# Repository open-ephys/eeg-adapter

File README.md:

eeg-adapter
===========

Adapters for using open-ephys for human EEG

Also see the wiki category at https://open-ephys.atlassian.net/wiki/display/OEW/EEG for more info.

Specifications
-----------

EEG breakout board currently supports two connector types: P50 and 40 PIN

- P50 connector Manufactured by EASYCAP (Germany) 
   - **Compatible Systems:** BrainVision (BrainProducts, GmbH) 
   - **Channels:** 32+ channels
   - **Caps:** actiCAP, BrainCap Fast'nEasy, EasyCap, EasyCap active, Fast'nEasy Cap.
   - **Pitch:** 0.05"
   - **Ground:** Third column from the left, first pad at the bottom.
   - **Reference:** First column on the left, 7 pads up from the bottom.

- 40 PIN connector Manufactured by Compumedics Neuroscan (United States)
   - **Compatible Systems:** MagLink, CURRY Scan 7 (Neuroscan, USA)
   - **Channels:** 40+ Channels.
   - **Caps:** Quik-Cap.
   - **Pitch:** 0.1"
   - **Ground:** Bottom row 16 headers in from the left.
   - **Reference:** Top row 7 headers in from the left.

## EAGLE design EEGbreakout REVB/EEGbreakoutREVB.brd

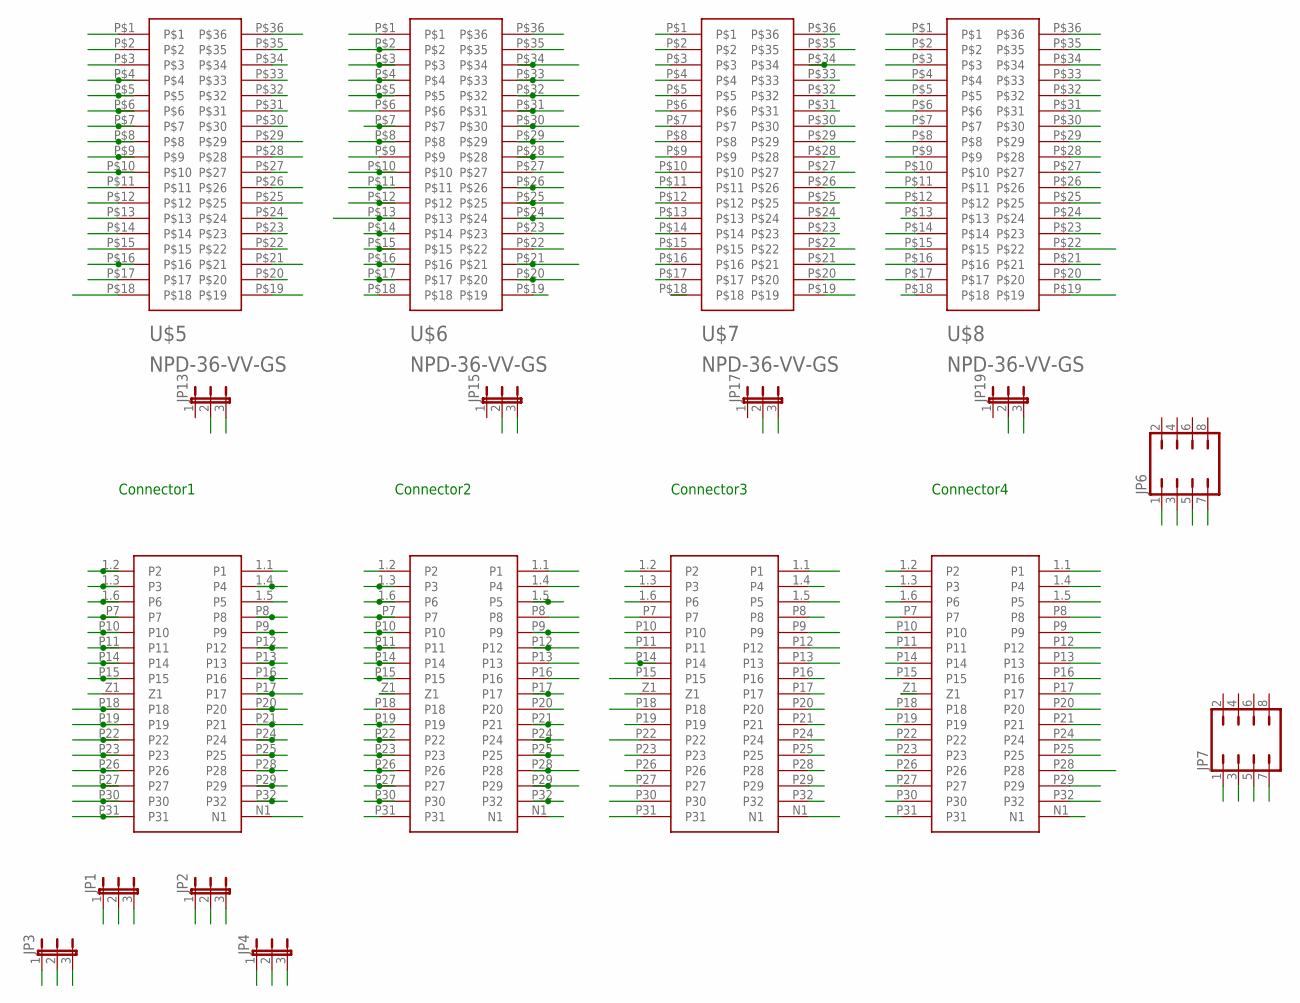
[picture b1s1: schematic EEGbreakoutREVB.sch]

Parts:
JP1, JP2, JP3, JP4, JP13, JP15, JP17, JP19: JP2E; JP2
JP6, JP7: JP4Q
U$1, U$2, U$3, U$4: P50; CON-MOLEX_71061-0003SM
U$5, U$6, U$7, U$8: NPD-36-VV-GS

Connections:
1.1: U$1.1.1 (P1), U$5.P$2
1.2: U$1.1.4 (P4), U$5.P$3
1.3: U$1.1.5 (P5), U$5.P$4
1.4: U$1.P8, U$5.P$5
1.5: U$1.P9, U$5.P$6
1.6: U$1.P12, U$5.P$7
1.7: U$1.P13, U$5.P$8
1.8: U$1.P16, U$5.P$9
1.9: U$1.P17, U$5.P$10
1.10: U$1.P20, U$5.P$11
1.11: U$1.P21, U$5.P$12
1.12: U$1.P24, U$5.P$13
1.13: U$1.P25, U$5.P$14
1.14: U$1.P28, U$5.P$15
1.15: U$1.P29, U$5.P$16
1.16: U$1.P32, U$5.P$17
1.17: U$1.1.2 (P2), U$5.P$20
1.18: U$1.1.3 (P3), U$5.P$21
1.20: U$1.P7, U$5.P$23
1.21: U$1.P10, U$5.P$24
1.22: U$1.P11, U$5.P$25
1.23: U$1.P14, U$5.P$26
1.24: U$1.P15, U$5.P$27
1.25: U$1.P18, U$5.P$28
1.26: U$1.P19, U$5.P$29
1.27: U$1.P22, U$5.P$30
1.28: U$1.P23, U$5.P$31
1.29: JP4.2, U$5.P$32
1.30: JP2.2, U$5.P$33
1.31: JP1.2, U$5.P$34
1.32: JP3.2, U$5.P$35
2.1: U$2.1.1 (P1), U$6.P$2
2.2: U$2.1.4 (P4), U$6.P$3
2.3: U$2.1.5 (P5), U$6.P$4
2.4: U$2.P8, U$6.P$5
2.5: U$2.P9, U$6.P$6
2.6: U$2.P12, U$6.P$7
2.7: U$2.P13, U$6.P$8
2.8: U$2.P16, U$6.P$9
2.9: U$2.P17, U$6.P$10
2.10: U$2.P20, U$6.P$11
2.11: U$2.P21, U$6.P$12
2.12: U$2.P24, U$6.P$13
2.13: U$2.P25, U$6.P$14
2.14: U$2.P28, U$6.P$15
2.15: U$2.P29, U$6.P$16
2.16: U$2.P32, U$6.P$17
2.17: U$2.1.2 (P2), U$6.P$20
2.18: U$2.1.3 (P3), U$6.P$21
2.19: U$2.1.6 (P6), U$6.P$22
2.20: U$2.P7, U$6.P$23
2.21: U$2.P10, U$6.P$24
2.22: U$2.P11, U$6.P$25
2.23: U$2.P14, U$6.P$26
2.24: U$2.P15, U$6.P$27
2.25: U$2.P18, U$6.P$28
2.26: U$2.P19, U$6.P$29
2.27: U$2.P22, U$6.P$30
2.28: U$2.P23, U$6.P$31
2.29: U$2.P26, U$6.P$32
2.30: U$2.P27, U$6.P$33
2.31: U$2.P30, U$6.P$34
2.32: U$2.P31, U$6.P$35
3.1: U$3.1.1 (P1), U$7.P$2
3.2: U$3.1.4 (P4), U$7.P$3
3.3: U$3.1.5 (P5), U$7.P$4
3.4: U$3.P8, U$7.P$5
3.5: U$3.P9, U$7.P$6
3.6: U$3.P12, U$7.P$7
3.7: U$3.P13, U$7.P$8
3.8: U$3.P16, U$7.P$9
3.9: U$3.P17, U$7.P$10
3.10: U$3.P20, U$7.P$11
3.11: U$3.P21, U$7.P$12
3.12: U$3.P24, U$7.P$13
3.13: U$3.P25, U$7.P$14
3.14: U$3.P28, U$7.P$15
3.15: U$3.P29, U$7.P$16
3.16: U$3.P32, U$7.P$17
3.17: U$3.1.2 (P2), U$7.P$20
3.18: U$3.1.3 (P3), U$7.P$21
3.19: U$3.1.6 (P6), U$7.P$22
3.20: U$3.P7, U$7.P$23
3.21: U$3.P10, U$7.P$24
3.22: U$3.P11, U$7.P$25
3.23: U$3.P14, U$7.P$26
3.24: U$3.P15, U$7.P$27
3.25: U$3.P18, U$7.P$28
3.26: U$3.P19, U$7.P$29
3.27: U$3.P22, U$7.P$30
3.28: U$3.P23, U$7.P$31
3.29: U$3.P26, U$7.P$32
3.30: U$3.P27, U$7.P$33
3.31: U$3.P30, U$7.P$34
3.32: U$3.P31, U$7.P$35
4.1: U$4.1.1 (P1), U$8.P$2
4.2: U$4.1.4 (P4), U$8.P$3
4.3: U$4.1.5 (P5), U$8.P$4
4.4: U$4.P8, U$8.P$5
4.5: U$4.P9, U$8.P$6
4.6: U$4.P12, U$8.P$7
4.7: U$4.P13, U$8.P$8
4.8: U$4.P16, U$8.P$9
4.9: U$4.P17, U$8.P$10
4.10: U$4.P20, U$8.P$11
4.11: U$4.P21, U$8.P$12
4.12: U$4.P24, U$8.P$13
4.13: U$4.P25, U$8.P$14
4.14: U$4.P28, U$8.P$15
4.15: U$4.P29, U$8.P$16
4.16: U$4.P32, U$8.P$17
4.17: U$4.1.2 (P2), U$8.P$20
4.18: U$4.1.3 (P3), U$8.P$21
4.19: U$4.1.6 (P6), U$8.P$22
4.20: U$4.P7, U$8.P$23
4.21: U$4.P10, U$8.P$24
4.22: U$4.P11, U$8.P$25
4.23: U$4.P14, U$8.P$26
4.24: U$4.P15, U$8.P$27
4.25: U$4.P18, U$8.P$28
4.26: U$4.P19, U$8.P$29
4.27: U$4.P22, U$8.P$30
4.28: U$4.P23, U$8.P$31
4.29: U$4.P26, U$8.P$32
4.30: U$4.P27, U$8.P$33
4.31: U$4.P30, U$8.P$34
4.32: U$4.P31, U$8.P$35
C1.29: JP4.1, U$1.P26
C1.30: JP2.1, U$1.P27
C1.31: JP1.1, U$1.P30
C1.32: JP3.1, U$1.P31
GND: JP13.3, JP15.3, JP17.3, JP19.3, U$1.N1, U$2.N1, U$3.N1, U$4.N1, U$5.P$1, U$5.P$19, U$6.P$1, U$6.P$19, U$7.P$1, U$7.P$19, U$8.P$1, U$8.P$19
J29: JP4.3, JP6.1
J30: JP2.3, JP6.3
J31: JP1.3, JP6.5
J32: JP3.3, JP6.7
unnamed: U$1.1.6 (P6), U$5.P$22
REF: JP7.1, JP13.2, U$1.Z1, U$5.P$18, U$5.P$36
REF1: JP7.3, JP15.2, U$2.Z1, U$6.P$18, U$6.P$36
REF2: JP7.5, JP17.2, U$3.Z1, U$7.P$18, U$7.P$36
REF3: JP7.7, JP19.2, U$4.Z1, U$8.P$18, U$8.P$36

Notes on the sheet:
Connector1
Connector2
Connector3
Connector4

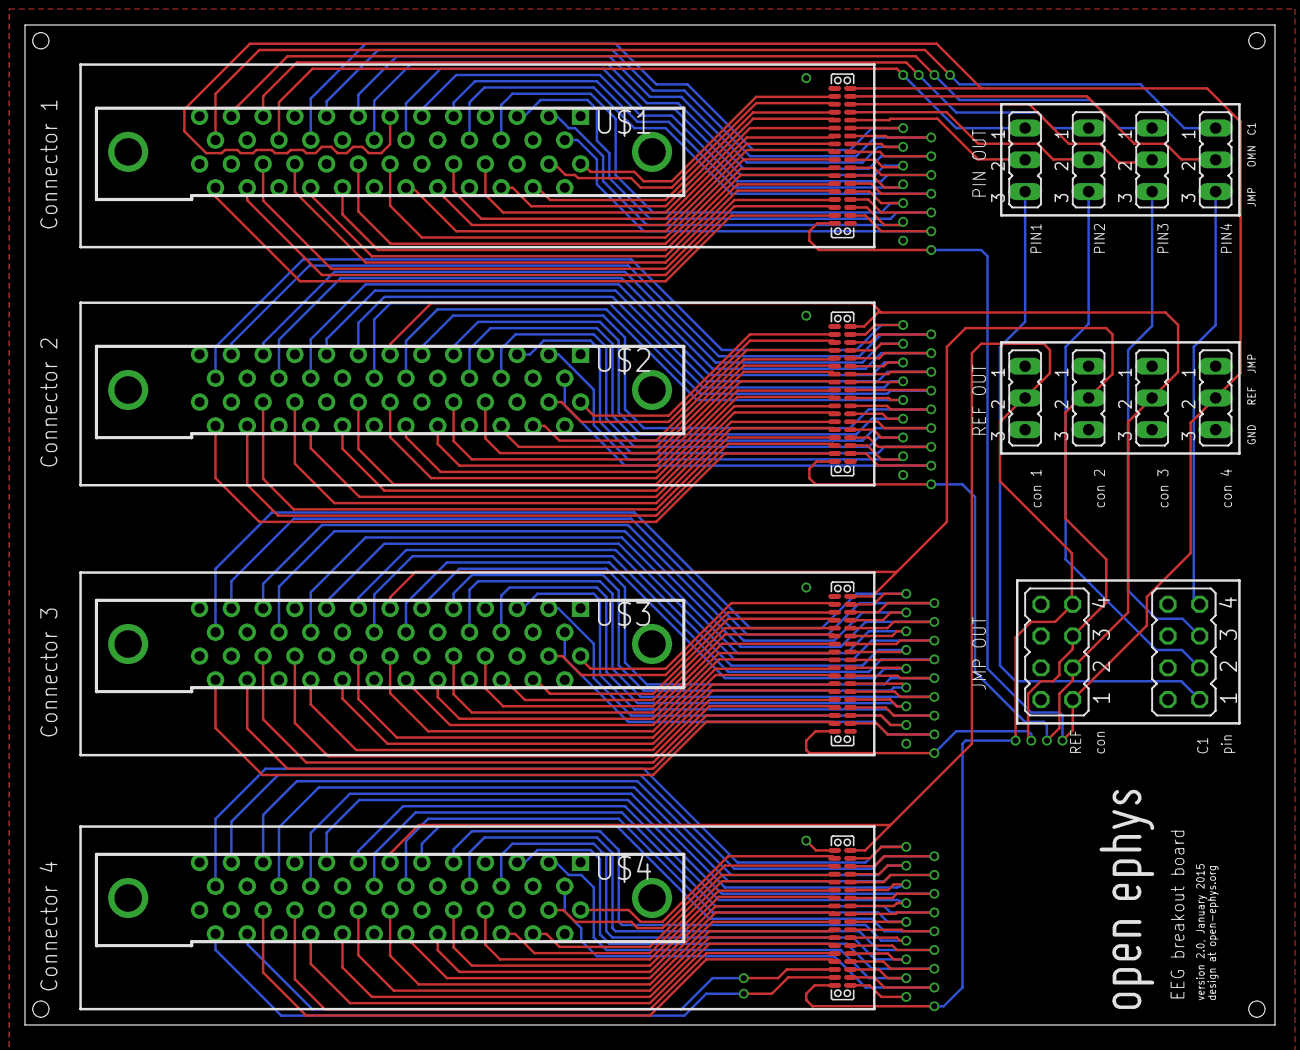
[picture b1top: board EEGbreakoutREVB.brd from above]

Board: 2 copper layers, 100.0 x 80.0 mm, 19 parts (0 on the bottom side), 141 nets.

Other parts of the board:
U$9: OPEN_EPHYS_LOGO

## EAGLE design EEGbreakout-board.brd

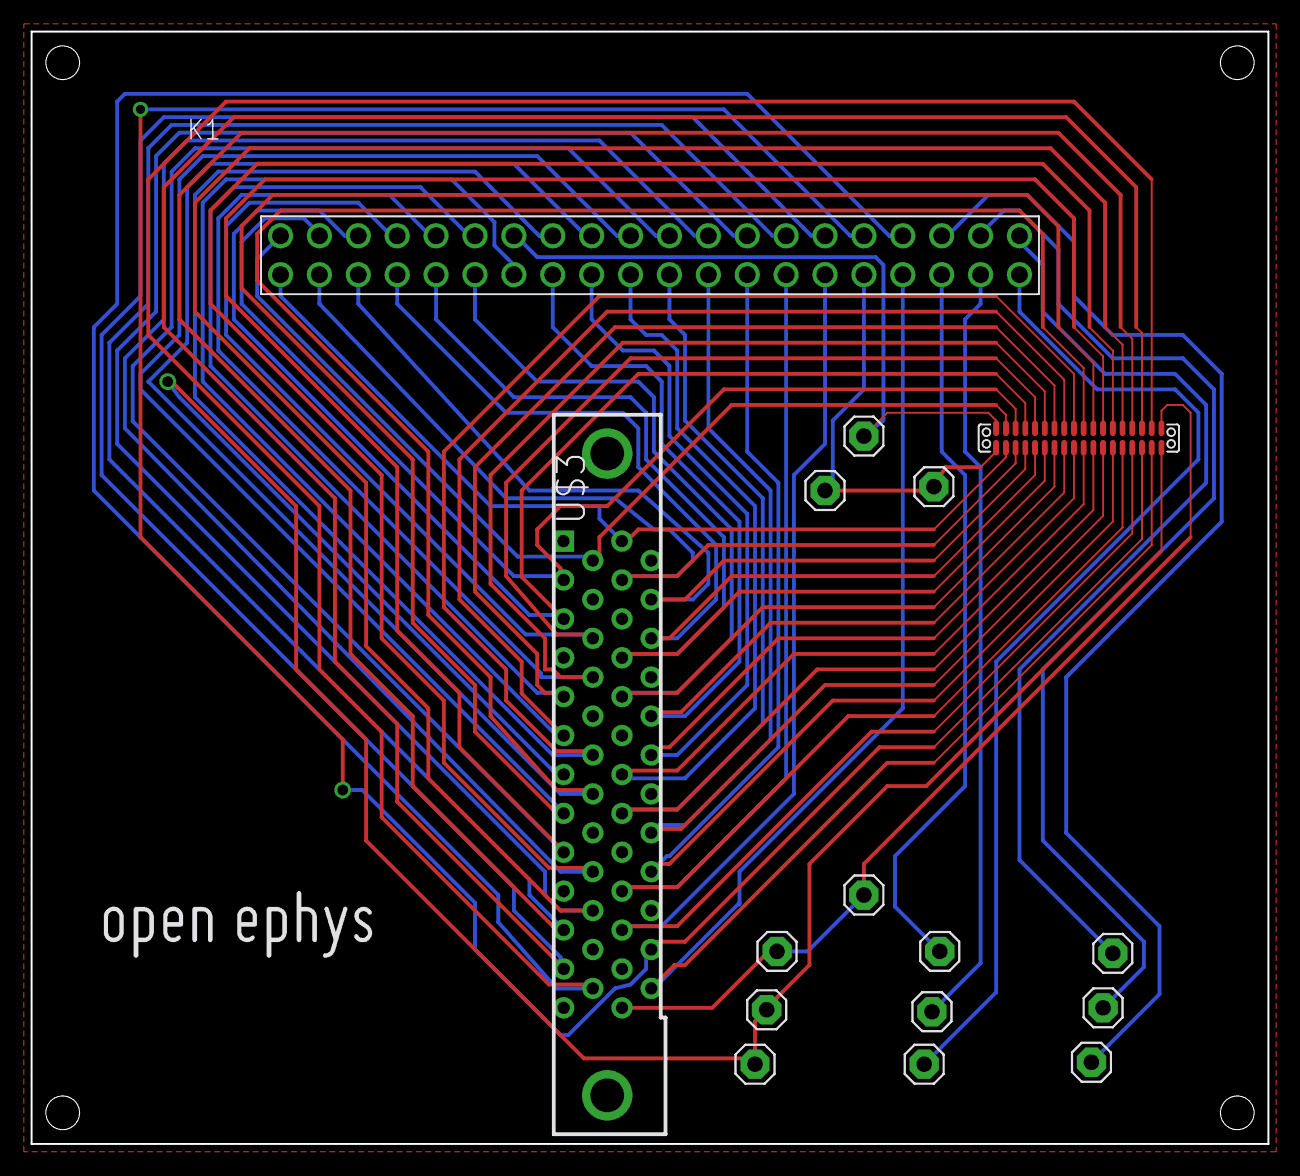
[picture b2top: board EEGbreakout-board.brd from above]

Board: 2 copper layers, 80.8 x 72.6 mm, 17 parts (0 on the bottom side), 40 nets.

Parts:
GND: 1X01
JP1, JP2, JP3, JP4, JP5, JP6, JP7, JP8, JP9, JP10, JP11, JP12: 1X01
K1: 61304021121
U$1: OPEN_EPHYS_LOGO
U$2: NPD-36-VV-GS
U$3: EZCF; CON-MOLEX_71061-0003SM

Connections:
GND: GND.1, JP7.1, JP8.1, JP9.1, K1.25, U$2.P$1, U$2.P$19, U$3.N1
unnamed: JP6.1, K1.1
unnamed: JP5.1, K1.2
unnamed: JP4.1, K1.3
unnamed: JP3.1, K1.23
unnamed: JP2.1, K1.22
unnamed: JP1.1, K1.21
unnamed: K1.20, U$2.P$35, U$3.P2
unnamed: K1.19, U$2.P$34, U$3.P3
unnamed: K1.18, U$2.P$33, U$3.P6
unnamed: K1.17, U$2.P$32, U$3.P7
unnamed: K1.16, U$2.P$31, U$3.P10
unnamed: K1.15, U$2.P$30, U$3.P11
unnamed: K1.34, U$2.P$29, U$3.P14
unnamed: K1.13, U$2.P$28, U$3.P15
unnamed: K1.12, U$2.P$27, U$3.P18
unnamed: K1.11, U$2.P$26, U$3.P19
unnamed: K1.10, U$2.P$25, U$3.P22
unnamed: K1.9, U$2.P$24, U$3.P23
unnamed: K1.8, U$2.P$23, U$3.P26
unnamed: K1.7, U$2.P$22, U$3.P27
unnamed: K1.6, U$2.P$21, U$3.P30
unnamed: K1.4, U$2.P$20, U$3.P31
unnamed: K1.24, U$2.P$17, U$3.P32
unnamed: K1.5, U$2.P$16, U$3.P29
unnamed: K1.26, U$2.P$15, U$3.P28
unnamed: K1.27, U$2.P$14, U$3.P25
unnamed: K1.28, U$2.P$13, U$3.P24
unnamed: K1.29, U$2.P$12, U$3.P21
unnamed: K1.30, U$2.P$11, U$3.P20
unnamed: K1.31, U$2.P$10, U$3.P17
unnamed: K1.32, U$2.P$9, U$3.P16
unnamed: K1.33, U$2.P$8, U$3.P13
unnamed: K1.35, U$2.P$7, U$3.P12
unnamed: K1.36, U$2.P$6, U$3.P9
unnamed: K1.37, U$2.P$5, U$3.P8
unnamed: K1.38, U$2.P$4, U$3.P5
unnamed: K1.39, U$2.P$3, U$3.P4
unnamed: K1.40, U$2.P$2, U$3.P1
REF: JP10.1, JP11.1, JP12.1, K1.14, U$2.P$18, U$2.P$36, U$3.Z1

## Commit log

2014-01-19 Create EEGbreakout-board.brd
    adapter layout for P50 and 40 pin connector
2014-01-19 Remove part description info that Eagle v6.3 had trouble loading
2014-01-23 EEG breakout Gerber
    Sunstone Gerber files for EEG adapter board
2014-01-23 Create EEGbreakout connector info
    Connector Specs for EEG adapter
2014-01-25 added wiki link
2014-03-12 Update for EEG adapter
    Contains Gerber files for PCB production by Seeed Studios
2017-03-17 EEG breakoutboard REVB
    Second version of EEG breakoutboard. Allows for up to 128 channels of EEG, with up to four interchangeable channels for other ephys measurements.
